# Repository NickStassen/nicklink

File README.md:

# NickLink v1.3

NickLink is a compact STM32F103C8T6 development and breakout board. Version 1.3 is a **34.0 × 25.5 mm, two-layer PCB** with an on-board **6-axis IMU (ST LSM6DSV)** for motion tracking, robotics and tap-to-wake projects. It also has two **2×10, 2.54 mm headers**, **four M2 mounting holes**, USB-C, RESET and BOOT buttons, a user LED, and **every header pin labelled on the front silkscreen**.

<details><summary>True size on a 27-inch 1440p monitor (view at 100% zoom)</summary>

</details>

**Real boards: v1.0 (left) vs v1.3 (right)**

**New board?** Follow the [bring-up guide](docs/BRINGUP.md): wiring for an STLINK-V3MINIE, a prebuilt USB DFU bootloader and test firmware, and a checklist for every part. After one ST-Link flash, the board is updated and tested over USB-C alone.

## What changed

**v1.3** adds the IMU on I2C1. It fits into existing gaps beside the MCU, on the top side with single-sided assembly. The board is 0.8 mm wider than v1.2 only because the pin labels grew to JLC's 1.0 mm minimum text height (see [JLCPCB design rules](#jlcpcb-design-rules)). PB6/PB7 get 4.7 kΩ pull-ups again, because the bus now has an on-board device. The IMU's INT1 drives PA0. The 3V3 budget drops by about 1 mA for the IMU. Everything else is as in v1.2.

**v1.3 reliability pass** (from a five-reviewer audit, the SPICE benches in [`sim/`](sim/) and ST's AN2586/AN4879 checklists):

- **Hot-plug damping:** R12, 1 Ω in series with VBUS, holds the USB hot-plug peak to 5.38 V and inrush under 50 µC. A ring on the 5V pin can still go higher. The regulator survives that because it is the 18 V TLV76733, not because every peak stays under 6 V.
- **Protected 5V pin:** J1.1 now has a 0.5 A polyfuse (F1) and a reverse-polarity P-MOSFET (Q1), so a short or a reversed supply no longer reaches VSYS unprotected.
- **D+ pull-up from VBUS** (AN4879 §3.1.1): it is present only while USB is plugged in. Powering from J1.1 no longer back-feeds the host.
- **Decoupling:** C4 at VDD3 is now 4.7 µF, as DS5319 requires. C12 (LDO input) is 4.7 µF, to keep inrush down.
- **User LED:** R6 is 330 Ω: about 1.3 mA instead of 0.4 mA, still within PC13's 3 mA sink limit.
- **Routing:** locked tracks for the USB-C orientation ties and the IMU's 3V3 feed. Every GND pad and pour island is checked for connection.

**Revision comparison:**

| | v1.1 | v1.2 | v1.3 |
|---|---|---|---|
| Outline | 34 × 33 mm (1122 mm²) | **33.19 × 25.5 mm** (846 mm², −25%) | **33.99 × 25.5 mm** (867 mm², −23%) |
| Pin labels | Numbered table on the back | **Name beside every pin on the front**; cheat sheet on the back | Same; 1.0 mm text (JLC minimum) |
| 5 V on the headers | None | **J1.1 = 5 V** (USB VBUS through a Schottky; also a 5 V input) | Same, plus a **0.5 A polyfuse and reverse-polarity protection** |
| USB power path | VBUS straight to the regulator | Schottky | **1 Ω hot-plug damping** + Schottky |
| Regulator | AMS1117-3.3 (SOT-223) + 22 µF tantalum | **TLV75533** (2×2 mm WSON) + ceramics | **TLV76733**, same package, input rated to 18 V |
| Reset | Header pin only | **RESET button** + NRST on J3 next to SWD | Same |
| Boot | BOOT0 slide switch | **BOOT button** (hold BOOT, tap RESET) | Same |
| SWD | Split across J1 and J3 | **All on J3**: 3V3, GND, SWDIO, SWCLK, SWO, NRST | Same |
| HSE crystal | 16 MHz | **8 MHz** (matches Blue Pill / STM32duino / CubeMX defaults) | Same |
| USB D+ pull-up | 1.5 kΩ to 3V3 | 1.5 kΩ to 3V3 | **From VBUS** (2.2k/4.7k), so no back-feed when powered from J1.1 |
| USB ESD | None | **USBLC6-2P6** on D+/D− and VBUS | Same |
| I2C pull-ups | 1.5 kΩ fitted on PB6/PB7 | Removed | **4.7 kΩ** (needed by the on-board IMU) |
| LEDs | Power | Power + **user LED on PC13** (low = on) | Same, brighter (330 Ω, about 1.3 mA) |
| IMU | — | — | **LSM6DSV** 6-axis accel + gyro with on-chip sensor fusion |
| Verification | — | DRC/ERC | DRC/ERC, SPICE benches ([`sim/`](sim/)), emulated test firmware ([`firmware/`](firmware/)) |

## Hardware

- STM32F103C8T6 (LQFP-48) with an 8 MHz crystal (12 pF load, 15 pF C0G caps): PLL ×9 = 72 MHz, USB clock 72 / 1.5 = 48 MHz.
- USB-C (GCT USB4085, through-hole) for power and USB full speed; 5.1 kΩ CC pull-downs for either orientation; D+ pull-up from VBUS (2.2 kΩ / 4.7 kΩ divider, 1.5 kΩ to 3.4 V, so it is present only while USB is plugged in); USBLC6-2P6 ESD array.
- Power path: USB VBUS → R12 1 Ω (hot-plug damping) → 1N5819WS Schottky → **VSYS** → TLV76733 LDO → **3V3** (J3.1, J1.20). VSYS also reaches the **5V pin** (J1.1) through a 0.5 A polyfuse (F1) and a reverse-polarity P-MOSFET (Q1). The Schottky stops a supply on the 5V pin from back-feeding the USB host.
- RESET button (NRST to GND, 100 nF), BOOT button (BOOT0 to 3V3, 10 kΩ pull-down), 10 kΩ pull-down on PB2/BOOT1.
- Red power LED, green user LED on PC13 (active low).
- **IMU:** ST LSM6DSV 6-axis accelerometer and gyroscope on I2C1 (PB6 SCL / PB7 SDA, address **0x6A**), INT1 to PA0.
- 33 GPIO + NRST on the headers. Only PA11/PA12 (USB) and PD0/PD1 (crystal) are not broken out.
- GND pours on both layers, stitched with vias.

## Header pinout

**Top view, USB at the top: J3 is left, J1 is right.** Pin 1 is the square pad at the upper left of each header; odd pins are the left column. The front silkscreen prints each pin's name right beside it (`A9` = PA9, `B12` = PB12, `RST` = NRST).

| Pin | J3 (left) | J1 (right) |
|---:|---|---|
| 1 | `3V3` 3V3 regulated output | `5V` 5 V (USB VBUS through Schottky + 0.5 A polyfuse; 4.5–5.5 V input, reverse-polarity protected) |
| 2 | `GND` | `GND` |
| 3 | `A9` PA9 / UART1 TX | `B15` PB15 / SPI2 MOSI |
| 4 | `A10` PA10 / UART1 RX | `B14` PB14 / SPI2 MISO |
| 5 | `A8` PA8 | `B13` PB13 / SPI2 SCK |
| 6 | `A15` PA15 | `B12` PB12 |
| 7 | `A13` PA13 / SWDIO | `B11` PB11 / I2C2 SDA / UART3 RX |
| 8 | `A14` PA14 / SWCLK | `B10` PB10 / I2C2 SCL / UART3 TX |
| 9 | `B3` PB3 / SWO | `B2` PB2 / BOOT1, 10k pull-down |
| 10 | `RST` NRST (reset, active low; 3.3 V only) | `B1` PB1 (3.3 V only) |
| 11 | `B4` PB4 | `B0` PB0 (3.3 V only) |
| 12 | `B5` PB5 (3.3 V only) | `A7` PA7 / SPI1 MOSI (3.3 V only) |
| 13 | `B6` PB6 / I2C1 SCL (4.7k pull-up, IMU; 3.3 V only) | `A6` PA6 / SPI1 MISO (3.3 V only) |
| 14 | `B7` PB7 / I2C1 SDA (4.7k pull-up, IMU; 3.3 V only) | `A5` PA5 / SPI1 SCK (3.3 V only) |
| 15 | `B8` PB8 / CAN RX (remap) | `A4` PA4 (3.3 V only) |
| 16 | `B9` PB9 / CAN TX (remap) | `A3` PA3 / UART2 RX (3.3 V only) |
| 17 | `C13` PC13 / user LED (3.3 V only) | `A2` PA2 / UART2 TX (3.3 V only) |
| 18 | `C14` PC14 (3.3 V only) | `A1` PA1 (3.3 V only) |
| 19 | `C15` PC15 (3.3 V only) | `A0` PA0 / WKUP / IMU INT1 via 10k (3.3 V only) |
| 20 | `GND` | `3V3` 3V3 regulated output |

Pins not marked "3.3 V only" are 5 V tolerant (FT) while the board is powered. B6/B7 are FT on the MCU but not at board level, because the IMU on that bus is limited to 3.6 V. PA1–PA7, PB0 and PB1 are also ADC inputs. PA0 is too, but it has the IMU interrupt on it (below). [`docs/pinout.csv`](docs/pinout.csv) has the same table in machine-readable form.

- **SWD:** J3.1 3V3 (target voltage sense), J3.2 GND, J3.7 SWDIO, J3.8 SWCLK, J3.10 NRST, optional J3.9 SWO.
- **USB bootloader:** the F103 has no factory USB DFU bootloader, so [`firmware/bootloader/`](firmware/bootloader/) adds one (dapboot, in the first 8 KiB of flash). Programs are linked at 0x08002000 and loaded over USB-C with `dfu-util`. Enter it with a double-tap of RESET, or J1.9 to 3V3 at reset.
- **Serial bootloader:** hold BOOT, tap RESET, release BOOT, then use USART1 on J3.3 (TX) / J3.4 (RX). This is ST's factory USART bootloader, in ROM, so it always works for recovery.
- **I2C1 / IMU:** I2C1 has on-board 4.7 kΩ pull-ups. External I2C modules can share the bus as long as they avoid address 0x6A and **pull up to 3.3 V only**. A 5 V module needs a level shifter, because the IMU's SCL/SDA limit is 3.6 V. If modules bring their own pull-ups, keep the combined value above about 1.5 kΩ. The 4.7 kΩ pull-ups meet the 400 kHz rise-time limit up to about 75 pF of bus capacitance (roughly 30 cm of wiring plus a few modules); for longer runs, use 100 kHz.
- **A0 has the IMU's INT1 on it through 10 kΩ.** INT1 drives low whenever no interrupt is asserted, so A0 always sees a 10 kΩ pull-down (also with INT1 set to open-drain, which only releases the pin while active-high). The interrupt is active high, matching WKUP's rising edge. You can still drive A0 from outside, or use it as an ADC input from a low-impedance source. Making A0 truly high-impedance needs INT1 set active-low open-drain (`H_LACTIVE` + `PP_OD`, IF_CFG 03h), which inverts the interrupt and stops it from waking the MCU through WKUP.
- **J3.6/J3.9/J3.11 (PA15/PB3/PB4) are JTAG pins at reset:** PA15 and PB4 have internal pull-ups and PB3 (JTDO/SWO) has none, until firmware frees them (`__HAL_AFIO_REMAP_SWJ_NOJTAG()` keeps SWD and releases them). PA13/PA14 stay SWD unless you disable SWJ completely, after which the debugger has to connect under reset (NRST is on J3.10).
- **User LED:** PC13 low turns it on. PC13–PC15 are low-drive pins (≤2 MHz) and must not source current. Their 3 mA sink limit is shared by all three pins (DS5319 Table 5), and the LED already takes about 1.3–1.8 mA of it. J3.17 carries the LED load, so an undriven PC13 floats around 1–1.5 V.

## IMU

The LSM6DSV is a 6-axis IMU: accelerometer up to ±16 g, gyroscope up to ±4000 dps.
- **Address:** I2C1 at 0x6A (SA0 tied low); CS is tied high for I2C mode.
- **Interrupt:** INT1 goes to PA0. PA0 is also the STM32's WKUP pin, so a tap or motion interrupt (rising edge) can wake the MCU from Standby.

### Axes

The IMU is placed at 0°, so its axes line up with the board and its readings need no remapping. Seen from the top with USB-C at the top edge (the same view as the [header pinout](#header-pinout)):

```
             USB-C
      +------[___]------+
      | J3           J1 |        +Y  toward USB-C
      | o o         o o |         ^
      | o o  [MCU]  o o |         |
      | o o     [U4]o o |         +----> +X  toward J1
      | o o         o o |        +Z  out of the component side, toward you
      +-----------------+
```

- **+X** points right, toward J1.
- **+Y** points up, toward the USB-C connector.
- **+Z** points out of the component side.

The axes are right-handed, and the gyroscope follows the right-hand rule. For example, positive gz is a counter-clockwise turn as seen from above. The accelerometer measures the reaction to gravity, so whichever axis points up reads +1 g:

| Board position | Reads +1 g on |
|---|---|
| Flat, components up | +Z |
| Flat, upside down | −Z |
| USB-C pointing up | +Y |
| USB-C pointing down | −Y |
| On its J3 edge (J1 up) | +X |
| On its J1 edge (J3 up) | −X |

The "flat" and "USB-C up" rows were measured on a v1.3 board; the rest follow from the right-handed axes. The test firmware's `imu` and `stream` commands report accel and gyro in these axes. [`firmware/imu_viewer.py`](firmware/README.md#3d-imu-viewer) shows the board's orientation live in 3D over USB-C.

Features useful here:
- **On-chip sensor fusion (SFLP):** outputs a game rotation vector (quaternion) at 15–480 Hz through the FIFO. The F103 has no hardware floating point, so this saves it doing the orientation math.
- **Hardware event detection:** tap, double-tap, wake-up, free-fall and 6D-orientation events, routable to INT1 (MD1_CFG 5Eh, with INTERRUPTS_ENABLE set in FUNCTIONS_ENABLE 50h). This covers tap-activated projects without polling.

Firmware starting points: ST's LSM6DSV platform-independent C driver, or the LSM6DSV16X one (`lsm6dsv16x-pid`) restricted to features the LSM6DSV has. Bring-up check: WHO_AM_I (0Fh) should read **0x70**.

**Why the LSM6DSV and not the LSM6DSV16X:** v1.3 was designed around the LSM6DSV16X (C5267406), but JLC lists that part as "Standard PCBA only" (X-ray inspection), and NickLink is an Economic PCBA board. The LSM6DSV (C41785564, which JLC lists as "LSM6DSVETR" and allows on Economic PCBA) is its sibling in the same LGA-14 package, with the same pinout, I2C-mode wiring, register map, WHO_AM_I and SFLP fusion. It lacks the LSM6DSV16X's machine-learning core, Qvar electrostatic sensing and analog hub. None of these is used here: Qvar and the analog hub need pins 2/3, which are tied to GND. The board and the test firmware are unchanged. ST's own store lists the part as LSM6DSV/LSM6DSVTR, so the "LSM6DSVETR" code is JLC's/LCSC's; confirm WHO_AM_I and SFLP output on the first boards.

Placement follows ST's LGA guidance: the IMU sits on the top side, with no ground pour or vias under the package, and only short pad-to-pad links at its edges. The local wiring is pre-routed; see docs/REVIEW.md. It sits in the right channel beside the MCU, below the RESET button, away from the regulator's heat and USB cable strain. ST's guidance of about 10 mm from screws (in its MEMS layout notes) can't be met on a board this small; H4 is about 2.4 mm from the IMU body. Mount on standoffs without over-tightening, since board flex shows up as accelerometer offset.

## Power

- **5V pin (J1.1), as an output:** VSYS through F1 (0.5 A hold, 1 A trip) and Q1. On USB that is VBUS minus the drop across R12, D2, F1 and Q1:
  - About 4.7 V at light load.
  - 4.2–4.4 V with 200 mA drawn from J1.1, from a 5.0 V port. From a 4.75 V port it is 4.0–4.1 V, so 5 V modules that need at least 4.5 V may not run.
  - A short from J1.1 to the adjacent GND pin trips F1 in about 0.1 s. VSYS collapses meanwhile, so the MCU resets once; the board recovers when the short is removed.
  - F1's hold current falls to about 0.33 A at 60 °C.
- **5V pin (J1.1), as an input:** apply 4.5–5.5 V and **do not exceed 5.5 V** in steady state. The parts behind it are rated higher (regulator 18 V, C12 and F1 16 V, Q1 gate ±12 V), so plug-in overshoot is survivable with normal leads. Q1 blocks a reversed supply, and F1 limits the current. D2 keeps J1.1 from back-feeding the USB host. With USB unplugged, the D+ pull-up is unpowered, so the host sees no device until USB is connected. Don't connect a battery to J1.1 while USB is plugged in: USB would charge it through F1 and Q1.
- **3V3 pins (J3.1, J1.20):** LDO outputs. Budget about **250 mA total including the MCU** when powered from USB. That figure is an estimate for this two-layer board (with two thermal vias under the LDO), not a measured limit. From a 5.5 V input on J1.1, keep below about 200 mA. **Do not feed 3V3 in from outside**: the regulator isn't specified for reverse current.
- **Hot-plug:** cables ring when plugged into a live supply. SPICE (`sim/` benches 11 and 12):
  - **USB:** with R12 fitted, the worst-case regulator input peak is 5.38 V for cables up to 1 µH (6.1–11.4 V without R12), and 7.3 V for an unusually long 3 µH cable. Inrush is 33 µC (USB limit 50 µC). R12 costs about 0.25 V of headroom at 250 mA.
  - **J1.1:** this path has no R12, so plugging a live supply onto J1.1 rings VSYS to about 5.4–9 V. That is why the regulator is the 18 V TLV76733.
  - **Bench leads over about 1 µH:** with these on J1.1, connect first and then switch the supply on. The most pessimistic capacitor model puts the ring past Q1's 12 V gate rating.

## Mounting

Four 2.2 mm holes for M2 screws. The keep-out is sized for **button-head (ISO 7380, 3.5 mm head)** screws and standoffs up to 4 mm across. Coordinates are measured from the board's upper-left corner, top view, X right, Y down.

| Hole | X (mm) | Y (mm) |
|---|---:|---:|
| H1 | 9.93 | 2.05 |
| H2 | 24.06 | 2.05 |
| H3 | 9.93 | 23.45 |
| H4 | 24.06 | 23.45 |

The USB-C receptacle overhangs the top edge by about 2 mm, as in v1.1.

## Open and edit

Open [`nicklink.kicad_pro`](nicklink.kicad_pro) in **KiCad 10**. The schematic, PCB, rules and project-local footprints (`nicklink.pretty/`) are included.

NickLink is generated by scripts in [`tools/`](tools/README.md). [`tools/spec.py`](tools/spec.py) is the single source of truth for parts, nets and header pinout, and [`tools/placement.py`](tools/placement.py) holds component positions. `tools/build_all.sh` regenerates the schematic, places parts, autoroutes with Freerouting, stitches the GND pours and runs DRC. It writes `nicklink.kicad_pcb` only if everything is clean. Everything runs in Docker (`kicad/kicad:10.0`); no local KiCad install is needed.

| Location | Contents |
|---|---|
| `nicklink.kicad_sch` / `.kicad_pcb` / `.kicad_pro` | Generated schematic, routed board, design rules |
| `nicklink.pretty/` | Project footprints: USB4085, plus header and button copies without silkscreen (the board draws its own labels) |
| `tools/` | Build pipeline, see [tools/README.md](tools/README.md) |
| `docs/` | [Design review](docs/REVIEW.md), pinout CSV, schematic, assembly and copper PDFs, renders |
| `fabrication/v1.3/` | Gerbers, drills, JLC BOM and CPL |
| `fabrication/v1.1/`, `v1.2/` | Previous revisions' outputs, kept for reference |
| `checks/` | Saved DRC/ERC reports for v1.3 |

## JLCPCB design rules

The board is checked against JLCPCB's published 2-layer and assembly limits ([PCB capabilities](https://jlcpcb.com/capabilities/pcb-capabilities), [assembly capabilities](https://jlcpcb.com/capabilities/pcb-assembly-capabilities), checked 2026-10-01). The limits are encoded in the board setup and `nicklink.kicad_dru`, so every DRC run enforces them.

| JLC limit | NickLink |
|---|---|
| Trace / space ≥ 0.10 / 0.10 mm | ≥ 0.10 mm tracks (0.127 mm signals, 0.2 mm GND and 3V3, 0.3 mm VBUS/5 V), 0.127 mm clearance |
| Via ≥ 0.15 mm drill / 0.25 mm diameter | 0.3 / 0.6 mm |
| Component PTH annular ring ≥ 0.18 mm | ≥ 0.18 mm. The USB4085 pads change from GCT's 0.40/0.65 mm (0.125 mm ring) to a 0.38 mm hole in a 0.74 mm pad, which stays within GCT's 0.40 ± 0.05 mm hole spec for the 0.22 × 0.15 mm pins. The pad gap is 0.11 mm, above JLC's 0.10 mm. The LDO's two thermal vias are 0.3 mm in 0.66 mm pads. |
| Pad hole-to-hole ≥ 0.45 mm; plated slot ≥ 0.5 mm | ≥ 0.47 mm (USB4085 0.85 mm pitch, 0.38 mm holes); 0.6 mm shield slots |
| SMD pad to pad ≥ 0.15 mm | ≥ 0.15 mm (the IMU's LGA is the tightest) |
| Copper to routed edge ≥ 0.2 mm (≥ 0.3 mm for Economic assembly) | 0.3 mm |
| Solder-mask web ≥ 0.10 mm | 0.10 mm minimum checked |
| Silkscreen line ≥ 0.15 mm, text ≥ 1.0 mm, silk to pad ≥ 0.15 mm | All silk ≥ 0.15 mm wide; labels 1.0 mm tall; labels 0.15 mm from pads and the edge. The library 0402 footprints' own silk sits about 0.09 mm from their pads; JLC clips it. |
| Component bodies ≥ 0.3 mm apart, IPC-7351B medium density | KiCad library courtyards (IPC nominal), none overlapping |
| Economic assembly: components ≥ 0.3 mm from edge, pitch ≥ 0.4 mm, passives ≥ 0201 | SMD bodies ≥ 1 mm from the edge; finest pitch 0.5 mm; 0402 passives |

**Ordering:**
- Under 70 × 70 mm, so order **Economic PCBA**. Economic needs no on-board fiducials or rails. JLC can add edge rails and fiducials if you choose Standard or panelize; on-board fiducials would need 3.85 mm from the edge.
- Choose an **ENIG** finish: the 0.5 mm-pitch LGA and LQFP solder more reliably on a flat pad than on HASL. On Economic PCBA, 1.6 mm ENIG comes only with **green** solder mask. Avoid black or white anyway: JLC only keeps a mask bridge between pads 0.13 mm or more apart on those colours (0.10 mm on green), and the USB-C pads are 0.11 mm apart.
- The CPL is in Gerber coordinates, so JLC aligns it to the board without an "offset" prompt. Its rotations and positions are corrected per LCSC part for JLC's own footprints (`JLC_ROT`/`JLC_OFS` in `tools/fab.sh`: LQFP-48 −90°; SOT-666 and SOT-323 +180°; the 2×10 headers −90° and centred; USB4085 origin offset). Still check the pin-1 marks in JLC's placement preview.
- JLC also assembles the through-hole parts (USB-C, headers; wave soldered), so the BOM has one line per LCSC part, THT included. The USB-C GND pins use thermal reliefs, which also helps if you ever hand-solder a replacement.
- Signal tracks, and VBUS_D (USB power) under H1, pass under the M2 screw heads (under solder mask, vias tented). Use plastic standoffs or washers if you clamp with metal hardware.

## Validation and fabrication

KiCad 10.0.6: **0 DRC violations, 0 unconnected items, 0 schematic-parity issues, 0 ERC errors or warnings** (reports in [`checks/`](checks/)). Every pin in the schematic netlist is checked against `tools/spec.py`. These checks cover connectivity and geometry. This revision has not been built yet; it needs a prototype and bench testing (see [`docs/BRINGUP.md`](docs/BRINGUP.md)).

The BOM carries verified LCSC part numbers for every part, through-hole included. To order, upload `fabrication/v1.3/nicklink_gerbers.zip`, then for assembly `nicklink_BOM_JLC.csv` and `nicklink_CPL.csv`. Several parts are JLC "Extended" parts, which add a per-part loading fee; see [`tools/parts_research.md`](tools/parts_research.md).

**Bring-up and board test:** [`docs/BRINGUP.md`](docs/BRINGUP.md) walks through the first power-up of a new board, wiring an STLINK-V3MINIE to J3 once to flash the USB bootloader and test firmware ([`firmware/prebuilt/`](firmware/prebuilt/)), and a checklist run over USB-C. The checklist covers power, crystal, LEDs, buttons, USB, IMU, every header GPIO, ADC and Standby wake.

**Interface limits:**

- USB and CAN cannot run at the same time on the F103 (they share packet RAM).
- **I2C1 is always in use by the IMU (PB6/PB7).**
  - Remapping SPI1 to PA15/PB3/PB4/PB5 while I2C1 is clocked breaks MOSI on PB5 (erratum ES096). Gate the I2C1 clock off while SPI1 is remapped.
  - Using PB6/PB7 for USART1-remap or TIM4 disturbs the IMU's bus.
  - Remapping I2C1 to PB8/PB9 disconnects the IMU and takes the CAN pins.
- **Never set the IMU's `IF_CFG.I2C_I3C_disable` bit.** With CS tied high and no power switch on the IMU, only a full power cycle recovers it.
- CAN uses PB8/PB9 through the remap and needs an external transceiver.
- USB impedance and compliance are not qualified.

**Firmware notes for reliability:**

- The F103 has power-on/power-down reset but **no brown-out reset**. Enable the PVD (for example at 2.9 V) and stop flash writes when it trips.
- Enable the clock security system (CSS). If the HSE fails, the MCU falls back to HSI. USB cannot run from HSI, so treat that as a fault.
- Do not drive header pins while the board is unpowered. Keep injected current within ±5 mA per pin; PA4, PA5 and PC13–PC15 tolerate none.
- Set unused pins to analog input (the lowest-power, defined state) and free JTAG with `NOJTAG` if PA15/PB3/PB4 are used as GPIO.

**Simulation and test firmware:** [`sim/`](sim/) holds ngspice benches for hot-plug, LDO, brown-out, reset, LEDs, I2C, VDDA and the crystal, with results in `sim/results/summary.md`. [`firmware/`](firmware/) is a bring-up firmware for this pinout. It exercises the user LED, RESET, every header GPIO, the IMU (including tap wake on A0), USART1 and the HSE/PLL with HSI fallback, and runs under Renode emulation (`firmware/test.sh`) before you flash the real board.

## References

- [ST STM32F103x8/xB datasheet](https://www.st.com/resource/en/datasheet/stm32f103c8.pdf)
- [ST AN2586 — hardware design](https://www.st.com/resource/en/application_note/an2586-getting-started-with-stm32f10xxx-hardware-development-stmicroelectronics.pdf)
- [ST AN2867 — oscillator design](https://www.st.com/resource/en/application_note/an2867-guidelines-for-oscillator-design-on-stm8afals-and-stm32-mcusmpus-stmicroelectronics.pdf)
- [TI TLV767 datasheet](https://www.ti.com/lit/ds/symlink/tlv767.pdf) (U2 from v1.3); [TLV755P](https://www.ti.com/lit/ds/symlink/tlv755p.pdf) (v1.2)
- [ST LSM6DSV datasheet](https://www.st.com/resource/en/datasheet/lsm6dsv.pdf)
- [ST USBLC6-2 datasheet](https://www.st.com/resource/en/datasheet/usblc6-2.pdf)

Licensed under the [MIT License](LICENSE).

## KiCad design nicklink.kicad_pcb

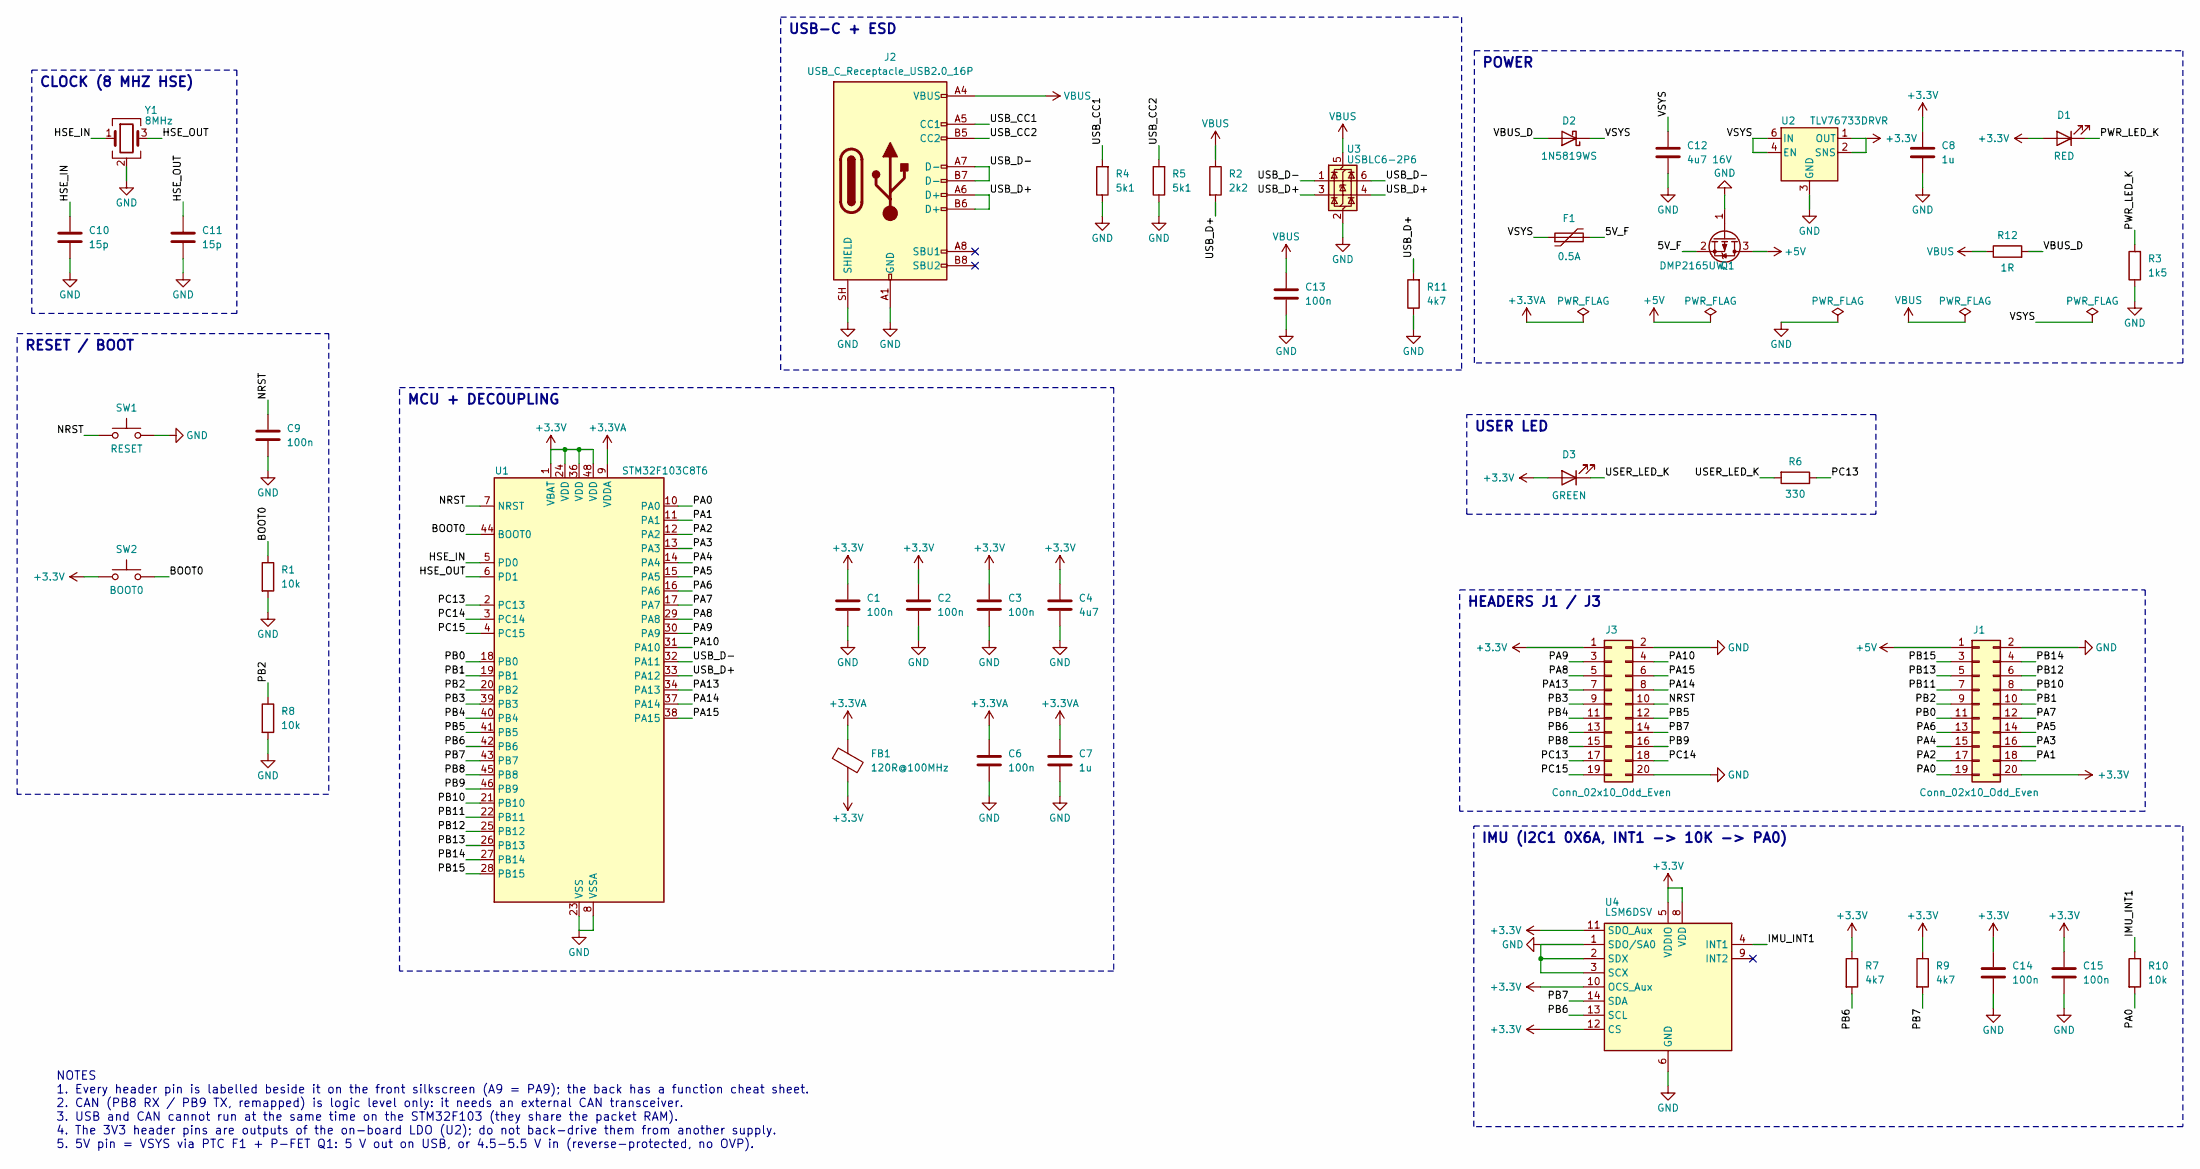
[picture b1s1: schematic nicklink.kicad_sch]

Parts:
C1, C2, C3, C6, C9, C13, C14, C15: 100n; C_0402_1005Metric; LCSC C1525
C4: 4u7; C_0402_1005Metric; LCSC C23733
C7, C8: 1u; C_0402_1005Metric; LCSC C52923
C10, C11: 15p; C_0402_1005Metric; LCSC C1548
C12: 4u7 16V; C_0402_1005Metric; MPN Samsung CL05A475MO5NUNC; LCSC C318563
D1: RED; LED_0402_1005Metric; MPN Everlight 16-213/R6C-AQ2R2B/3T; LCSC C264407
D2: 1N5819WS; D_SOD-323; LCSC C191023
D3: GREEN; LED_0402_1005Metric; MPN Everlight 16-213/GHC-YR1S1/3T; LCSC C74338
F1: 0.5A; Fuse_0805_2012Metric; MPN LUTE 0805L050/16XR; LCSC C22435898
FB1: 120R@100MHz; L_0402_1005Metric; LCSC C85812
J1, J3: Conn_02x10_Odd_Even; PinHeader_2x10_P2.54mm_Vertical_NoSilk; MPN HanElectricity 2541WV-2x10P (male, 6 mm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; LCSC C5383109
J2: USB_C_Receptacle_USB2.0_16P; USB_C_Receptacle_GCT_USB4085_EdgeSilk; MPN GCT USB4085-GF-A; LCSC C7095263
Q1: DMP2165UW; SOT-323_SC-70_NoSilk; MPN Diodes DMP2165UW-7; LCSC C388477
R1, R10: 10k; R_0402_1005Metric; LCSC C25744
R2: 2k2; R_0402_1005Metric; LCSC C25879
R3: 1k5; R_0402_1005Metric; LCSC C25867
R4: 5k1; R_0402_1005Metric; LCSC C25905
R5: 5k1; R_0402_1005Metric_NoSilk; LCSC C25905
R6: 330; R_0402_1005Metric; LCSC C25104
R7, R9: 4k7; R_0402_1005Metric; LCSC C25900
R8: 10k; R_0402_1005Metric_NoSilk; LCSC C25744
R11: 4k7; R_0402_1005Metric_NoSilk; LCSC C25900
R12: 1R; R_0805_2012Metric; MPN YAGEO SR0805FR-471RL; LCSC C873764
SW1: RESET; SW_SPST_B3U-1000P_NoSilk; LCSC C231329
SW2: BOOT0; SW_SPST_B3U-1000P_NoSilk; LCSC C231329
U1: STM32F103C8T6; LQFP-48_7x7mm_P0.5mm; LCSC C8734
U2: TLV76733DRVR; WSON-6-1EP_2x2mm_P0.65mm_EP1x1.6mm_ThermalVias03; MPN TI TLV76733DRVR; LCSC C2848334
U3: USBLC6-2P6; SOT-666; LCSC C15999
U4: LSM6DSV; LGA-14_3x2.5mm_P0.5mm_LayoutBorder3x4y_NoSilk; MPN ST LSM6DSV (JLC: LSM6DSVETR); LCSC C41785564
Y1: 8MHz; Crystal_SMD_3225-4Pin_3.2x2.5mm; MPN YXC X32258MOB4SI (CL 12 pF); LCSC C2682775

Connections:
+3.3V: C1.1, C2.1, C3.1, C4.1, C8.1, C14.1, C15.1, D1.2 (A), D3.2 (A), FB1.2, J1.20, J3.1, R7.1, R9.1, SW2.1, U1.1 (VBAT), U1.24 (VDD), U1.36 (VDD), U1.48 (VDD), U2.1 (OUT), U2.2 (SNS), U4.5 (VDDIO), U4.8 (VDD), U4.10 (OCS_Aux), U4.11 (SDO_Aux), U4.12 (CS)
+3.3VA: C6.1, C7.1, FB1.1, U1.9 (VDDA)
+5V: J1.1, Q1.3 (D)
/5V_F: F1.2, Q1.2 (S)
/BOOT0: R1.1, SW2.2, U1.44 (BOOT0)
/HSE_IN: C10.1, U1.5 (PD0), Y1.1
/HSE_OUT: C11.1, U1.6 (PD1), Y1.3
/IMU_INT1: R10.1, U4.4 (INT1)
/NRST: C9.1, J3.10, SW1.1, U1.7 (NRST)
/PA0: J1.19, R10.2, U1.10 (PA0)
/PA1: J1.18, U1.11 (PA1)
/PA2: J1.17, U1.12 (PA2)
/PA3: J1.16, U1.13 (PA3)
/PA4: J1.15, U1.14 (PA4)
/PA5: J1.14, U1.15 (PA5)
/PA6: J1.13, U1.16 (PA6)
/PA7: J1.12, U1.17 (PA7)
/PA8: J3.5, U1.29 (PA8)
/PA9: J3.3, U1.30 (PA9)
/PA10: J3.4, U1.31 (PA10)
/PA13: J3.7, U1.34 (PA13)
/PA14: J3.8, U1.37 (PA14)
/PA15: J3.6, U1.38 (PA15)
/PB0: J1.11, U1.18 (PB0)
/PB1: J1.10, U1.19 (PB1)
/PB2: J1.9, R8.1, U1.20 (PB2)
/PB3: J3.9, U1.39 (PB3)
/PB4: J3.11, U1.40 (PB4)
/PB5: J3.12, U1.41 (PB5)
/PB6: J3.13, R7.2, U1.42 (PB6), U4.13 (SCL)
/PB7: J3.14, R9.2, U1.43 (PB7), U4.14 (SDA)
/PB8: J3.15, U1.45 (PB8)
/PB9: J3.16, U1.46 (PB9)
/PB10: J1.8, U1.21 (PB10)
/PB11: J1.7, U1.22 (PB11)
/PB12: J1.6, U1.25 (PB12)
/PB13: J1.5, U1.26 (PB13)
/PB14: J1.4, U1.27 (PB14)
/PB15: J1.3, U1.28 (PB15)
/PC13: J3.17, R6.1, U1.2 (PC13)
/PC14: J3.18, U1.3 (PC14)
/PC15: J3.19, U1.4 (PC15)
/PWR_LED_K: D1.1 (K), R3.2
/USB_CC1: J2.A5 (CC1), R4.2
/USB_CC2: J2.B5 (CC2), R5.2
/USB_D+: J2.A6 (D+), J2.B6 (D+), R2.2, R11.2, U1.33 (PA12), U3.3 (I/O2), U3.4 (I/O2)
/USB_D-: J2.A7 (D-), J2.B7 (D-), U1.32 (PA11), U3.1 (I/O1), U3.6 (I/O1)
/USER_LED_K: D3.1 (K), R6.2
/VBUS_D: D2.2 (A), R12.2
/VSYS: C12.1, D2.1 (K), F1.1, U2.4 (EN), U2.6 (IN)
GND: C1.2, C2.2, C3.2, C4.2, C6.2, C7.2, C8.2, C9.2, C10.2, C11.2, C12.2, C13.2, C14.2, C15.2, J1.2, J2.A1 (GND), J2.A12 (GND), J2.B1 (GND), J2.B12 (GND), J2.SH (SHIELD), J3.2, J3.20, Q1.1 (G), R1.2, R3.1, R4.1, R5.1, R8.2, R11.1, SW1.2, U1.8 (VSSA), U1.23 (VSS), U1.35 (VSS), U1.47 (VSS), U2.3 (GND), U2.5 (GND), U2.7 (GND), U3.2 (GND), U4.1 (SDO/SA0), U4.2 (SDX), U4.3 (SCX), U4.6 (GND), U4.7 (GND), Y1.2 (G), Y1.4 (G)
VBUS: C13.1, J2.A4 (VBUS), J2.A9 (VBUS), J2.B4 (VBUS), J2.B9 (VBUS), R2.1, R12.1, U3.5 (VBUS)

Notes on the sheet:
CLOCK (8 MHZ HSE)
RESET / BOOT
MCU + DECOUPLING
USB-C + ESD
POWER
USER LED
HEADERS J1 / J3
IMU (I2C1 0X6A, INT1 -> 10K -> PA0)
NOTES 1. Every header pin is labelled beside it on the front silkscreen (A9 = PA9); the back has a function cheat sheet. 2. CAN (PB8 RX / PB9 TX, remapped) is logic level only: it needs an external CAN transceiver. 3. USB and CAN cannot run at the same time on the STM32F103 (they share the packet R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

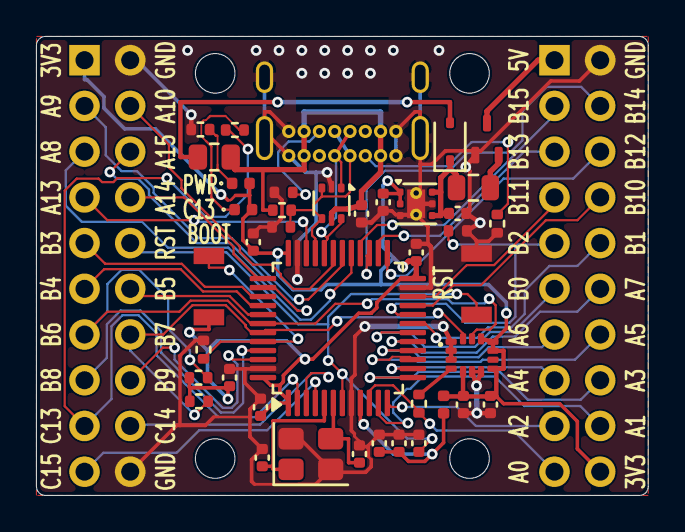
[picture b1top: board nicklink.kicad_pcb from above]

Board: 2 copper layers, 34.0 x 25.5 mm, 46 parts (0 on the bottom side), 52 nets.

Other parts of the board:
H1: H1; MountingHole_2.2mm_M2_ISO7380
H2: H2; MountingHole_2.2mm_M2_ISO7380
H3: H3; MountingHole_2.2mm_M2_ISO7380
H4: H4; MountingHole_2.2mm_M2_ISO7380

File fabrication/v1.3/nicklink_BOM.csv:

Comment,Designator,Footprint,LCSC Part #,Notes,Assembly
100n,"C1,C2,C3,C6,C9,C13,C14,C15",C_0402_1005Metric,C1525,"C1: VDD pin 1/VBAT decoupling; C2: VDD pin 24 decoupling; C3: VDD pin 36 decoupling; C6: VDDA; C13: USBLC6 VBUS decoupling; C14,C15: IMU VDD/VDDIO",SMD
4u7,C4,C_0402_1005Metric,C23733,VDD3 (pin 48) bulk: DS5319 Fig. 14 requires 4.7 uF on VDD3,SMD
1u,"C7,C8",C_0402_1005Metric,C52923,C7: VDDA; C8: LDO output,SMD
15p,"C10,C11",C_0402_1005Metric,C1548,C0G; crystal CL 12 pF,SMD
4u7 16V,C12,C_0402_1005Metric,C318563,"Samsung CL05A475MO5NUNC; LDO input, 16 V X5R (J1.1 hot-plug ring); USB allows <= 10 uF",SMD
RED,D1,LED_0402_1005Metric,C264407,Everlight 16-213/R6C-AQ2R2B/3T; Power,SMD
1N5819WS,D2,D_SOD-323,C191023,Blocks back-feed from VSYS / the 5V pin into USB,SMD
GREEN,D3,LED_0402_1005Metric,C74338,"Everlight 16-213/GHC-YR1S1/3T; User LED, PC13 low = on",SMD
0.5A,F1,Fuse_0805_2012Metric,C22435898,"LUTE 0805L050/16XR; 5V pin short / reverse-supply limit: Ihold 0.5 A, Itrip 1 A, 16 V",SMD
120R@100MHz,FB1,L_0402_1005Metric,C85812,,SMD
Conn_02x10_Odd_Even,"J1,J3",PinHeader_2x10_P2.54mm_Vertical_NoSilk,C5383109,"HanElectricity 2541WV-2x10P (male, 6 mm pins, 3 mm tail)",THT
USB_C_Receptacle_USB2.0_16P,J2,USB_C_Receptacle_GCT_USB4085_EdgeSilk,C7095263,GCT USB4085-GF-A,THT
DMP2165UW,Q1,SOT-323_SC-70_NoSilk,C388477,Diodes DMP2165UW-7; 5V pin reverse-polarity switch (gate to GND),SMD
10k,"R1,R8,R10",R_0402_1005Metric,C25744,R1: BOOT0 pull-down; R10: IMU INT1 isolation; R8: BOOT1 pull-down,SMD
2k2,R2,R_0402_1005Metric,C25879,"USB FS D+ pull-up (with R11: 1.5k to 3.4 V, VBUS-derived)",SMD
1k5,R3,R_0402_1005Metric,C25867,,SMD
5k1,"R4,R5",R_0402_1005Metric,C25905,,SMD
330,R6,R_0402_1005Metric,C25104,~1.2-1.8 mA (PC13 sinks <= 3 mA),SMD
4k7,"R7,R9,R11",R_0402_1005Metric,C25900,R7: I2C1 SCL pull-up; R9: I2C1 SDA pull-up; R11: D+ pull-up divider; VBUS bleed,SMD
1R,R12,R_0805_2012Metric,C873764,"YAGEO SR0805FR-471RL; Hot-plug damping (anti-surge, 500 mW)",SMD
BOOT0/RESET,"SW1,SW2",SW_SPST_B3U-1000P_NoSilk,C231329,SW2: Hold while resetting to enter the USART1 system bootloader,SMD
STM32F103C8T6,U1,LQFP-48_7x7mm_P0.5mm,C8734,,SMD
TLV76733DRVR,U2,WSON-6-1EP_2x2mm_P0.65mm_EP1x1.6mm_ThermalVias03,C2848334,TI TLV76733DRVR,SMD
USBLC6-2P6,U3,SOT-666,C15999,,SMD
LSM6DSV,U4,LGA-14_3x2.5mm_P0.5mm_LayoutBorder3x4y_NoSilk,C41785564,ST LSM6DSV (JLC: LSM6DSVETR),SMD
8MHz,Y1,Crystal_SMD_3225-4Pin_3.2x2.5mm,C2682775,YXC X32258MOB4SI (CL 12 pF),SMD

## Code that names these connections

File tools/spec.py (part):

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    # --- MCU ---------------------------------------------------------------
    "U1": ("MCU_ST_STM32F1:STM32F103C8Tx", "STM32F103C8T6", "Package_QFP:LQFP-48_7x7mm_P0.5mm", {
        "1": "+3.3V",  # VBAT, no backup battery
        "2": "PC13", "3": "PC14", "4": "PC15",
        "5": "HSE_IN", "6": "HSE_OUT", "7": "NRST",
        "8": "GND", "9": "+3.3VA",
        "10": "PA0", "11": "PA1", "12": "PA2", "13": "PA3", "14": "PA4",
        "15": "PA5", "16": "PA6", "17": "PA7", "18": "PB0", "19": "PB1",
        "20": "PB2", "21": "PB10", "22": "PB11", "23": "GND", "24": "+3.3V",
        "25": "PB12", "26": "PB13", "27": "PB14", "28": "PB15",
        "29": "PA8", "30": "PA9", "31": "PA10", "32": "USB_D-", "33": "USB_D+",
        "34": "PA13", "35": "GND", "36": "+3.3V",
        "37": "PA14", "38": "PA15", "39": "PB3", "40": "PB4", "41": "PB5",
        "42": "PB6", "43": "PB7", "44": "BOOT0", "45": "PB8", "46": "PB9",
        "47": "GND", "48": "+3.3V",
    }, {}),
    "C1": ("Device:C", "100n", "Capacitor_SMD:C_0402_1005Metric", {"1": "+3.3V", "2": "GND"}, {"Note": "VDD pin 1/VBAT decoupling"}),
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    "C7": ("Device:C", "1u", "Capacitor_SMD:C_0402_1005Metric", {"1": "+3.3VA", "2": "GND"}, {"Note": "VDDA"}),

    # --- Clock: 8 MHz HSE ---------------------------------------------------
    "Y1": ("Device:Crystal_GND24", "8MHz", "Crystal:Crystal_SMD_3225-4Pin_3.2x2.5mm", {"1": "HSE_IN", "2": "GND", "3": "HSE_OUT", "4": "GND"}, {"MPN": "YXC X32258MOB4SI (CL 12 pF)"}),
    "C10": ("Device:C", "15p", "Capacitor_SMD:C_0402_1005Metric", {"1": "HSE_IN", "2": "GND"}, {"Note": "C0G; crystal CL 12 pF"}),
    "C11": ("Device:C", "15p", "Capacitor_SMD:C_0402_1005Metric", {"1": "HSE_OUT", "2": "GND"}, {"Note": "C0G; crystal CL 12 pF"}),

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    "C9": ("Device:C", "100n", "Capacitor_SMD:C_0402_1005Metric", {"1": "NRST", "2": "GND"}, {}),
    "SW2": ("Switch:SW_Push", "BOOT0", "nicklink:SW_SPST_B3U-1000P_NoSilk", {"1": "+3.3V", "2": "BOOT0"}, {"Note": "Hold while resetting to enter the USART1 system bootloader"}),
    "R1": ("Device:R", "10k", "Resistor_SMD:R_0402_1005Metric", {"1": "BOOT0", "2": "GND"}, {"Note": "BOOT0 pull-down"}),
    "R8": ("Device:R", "10k", "nicklink:R_0402_1005Metric_NoSilk", {"1": "PB2", "2": "GND"}, {"Note": "BOOT1 pull-down"}),

    # --- USB ----------------------------------------------------------------
    "J2": ("Connector:USB_C_Receptacle_USB2.0_16P", "USB_C_Receptacle_USB2.0_16P", "nicklink:USB_C_Receptacle_GCT_USB4085_EdgeSilk", {
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    # R12 damps the USB cable inductance against the ceramic input caps on hot-plug (sim bench 11:
    # without it the input rings to about 6.1-11.4 V; with 1.0 ohm and C12 4.7 uF the USB peak is 5.38 V).
    # The fitted regulator is the TLV76733 (VIN/EN abs max 18 V). The 6.0 V figure was the TLV755 it replaced.
    "R12": ("Device:R", "1R", "Resistor_SMD:R_0805_2012Metric", {"1": "VBUS", "2": "VBUS_D"}, {"Note": "Hot-plug damping (anti-surge, 500 mW)", "MPN": "YAGEO SR0805FR-471RL"}),
    "D2": ("Device:D_Schottky", "1N5819WS", "Diode_SMD:D_SOD-323", {"1": "VSYS", "2": "VBUS_D"}, {"Note": "Blocks back-feed from VSYS / the 5V pin into USB"}),  # 1=K, 2=A
    "C12": ("Device:C", "4u7 16V", "Capacitor_SMD:C_0402_1005Metric", {"1": "VSYS", "2": "GND"}, {"Note": "LDO input, 16 V X5R (J1.1 hot-plug ring); USB allows <= 10 uF", "MPN": "Samsung CL05A475MO5NUNC"}),
    "F1": ("Device:Polyfuse", "0.5A", "Fuse:Fuse_0805_2012Metric", {"1": "VSYS", "2": "5V_F"}, {"Note": "5V pin short / reverse-supply limit: Ihold 0.5 A, Itrip 1 A, 16 V", "MPN": "LUTE 0805L050/16XR"}),
    # SOT-323 G-S-D = 1-2-3, same as the library's DMG2301L symbol (SOT-23); footprint overridden.
    "Q1": ("Transistor_FET:DMG2301L", "DMP2165UW", "nicklink:SOT-323_SC-70_NoSilk", {"1": "GND", "2": "5V_F", "3": "+5V"}, {"Note": "5V pin reverse-polarity switch (gate to GND)", "MPN": "Diodes DMP2165UW-7"}),
    # TLV76733DRVR (WSON-6 2x2, DRV0006A like the TLV755): 1 OUT, 2 SNS (tie to OUT), 3 GND, 4 EN, 5 GND,
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    # --- LEDs ---------------------------------------------------------------
    "D1": ("Device:LED", "RED", "LED_SMD:LED_0402_1005Metric", {"1": "PWR_LED_K", "2": "+3.3V"}, {"Note": "Power", "MPN": "Everlight 16-213/R6C-AQ2R2B/3T"}),  # 1=K, 2=A
    "R3": ("Device:R", "1k5", "Resistor_SMD:R_0402_1005Metric", {"1": "GND", "2": "PWR_LED_K"}, {}),
    "D3": ("Device:LED", "GREEN", "LED_SMD:LED_0402_1005Metric", {"1": "USER_LED_K", "2": "+3.3V"}, {"Note": "User LED, PC13 low = on", "MPN": "Everlight 16-213/GHC-YR1S1/3T"}),
    "R6": ("Device:R", "330", "Resistor_SMD:R_0402_1005Metric", {"1": "PC13", "2": "USER_LED_K"}, {"Note": "~1.2-1.8 mA (PC13 sinks <= 3 mA)"}),

    # --- IMU: LSM6DSV on I2C1 (address 0x6A), INT1 -> PA0 (WKUP) ----------------
    # Project symbol (nicklink.kicad_sym): KiCad has none; same LGA-14 pinout as LSM6DSM.
    # LSM6DSV (DS13476), not the LSM6DSV16X it replaced: JLC lists the LSM6DSV16X (C5267406) as
    # "Standard PCBA only". Same pinout, register map, WHO_AM_I 0x70 and SFLP sensor fusion; it lacks
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    "U4": ("nicklink:LSM6DSV", "LSM6DSV", "nicklink:LGA-14_3x2.5mm_P0.5mm_LayoutBorder3x4y_NoSilk", {
        "1": "GND",          # SDO/SA0 low -> I2C address 0x6A
        "2": "GND", "3": "GND",  # SDx/SCx aux bus unused
        "4": "IMU_INT1",     # INT1 -> R10 -> PA0 (INT1 drives low by default)
        "5": "+3.3V", "8": "+3.3V",  # VDDIO, VDD
        "6": "GND", "7": "GND",
        "10": "+3.3V", "11": "+3.3V",  # OCS_Aux/SDO_Aux: "connect to Vdd_IO or leave unconnected" (DS13476 Table 2)
        "12": "+3.3V",       # CS high -> I2C mode
        "13": "PB6", "14": "PB7",
    }, {"MPN": "ST LSM6DSV (JLC: LSM6DSVETR)"}),
    "C14": ("Device:C", "100n", "Capacitor_SMD:C_0402_1005Metric", {"1": "+3.3V", "2": "GND"}, {"Note": "IMU VDD/VDDIO"}),
    "C15": ("Device:C", "100n", "Capacitor_SMD:C_0402_1005Metric", {"1": "+3.3V", "2": "GND"}, {"Note": "IMU VDD/VDDIO"}),
    # INT1 is "output forced to ground" from power-up until firmware configures the IMU;
    # 10k keeps that from fighting whatever a user connects to A0 (it becomes a weak pull-down).
    "R10": ("Device:R", "10k", "Resistor_SMD:R_0402_1005Metric", {"1": "IMU_INT1", "2": "PA0"}, {"Note": "IMU INT1 isolation"}),
    "R7": ("Device:R", "4k7", "Resistor_SMD:R_0402_1005Metric", {"1": "+3.3V", "2": "PB6"}, {"Note": "I2C1 SCL pull-up"}),
    "R9": ("Device:R", "4k7", "Resistor_SMD:R_0402_1005Metric", {"1": "+3.3V", "2": "PB7"}, {"Note": "I2C1 SDA pull-up"}),

    # --- Headers ------------------------------------------------------------
    # Top view, USB up: J3 left, J1 right. Pin 1 upper-left; odd pins = left column. JLC assembles them (THT).
    "J1": ("Connector_Generic:Conn_02x10_Odd_Even", "Conn_02x10_Odd_Even", "nicklink:PinHeader_2x10_P2.54mm_Vertical_NoSilk", {
        "1": "+5V", "2": "GND",
        "3": "PB15", "4": "PB14", "5": "PB13", "6": "PB12",
        "7": "PB11", "8": "PB10", "9": "PB2", "10": "PB1",
        "11": "PB0", "12": "PA7", "13": "PA6", "14": "PA5",
        "15": "PA4", "16": "PA3", "17": "PA2", "18": "PA1",
        "19": "PA0", "20": "+3.3V",
    }, {"MPN": "HanElectricity 2541WV-2x10P (male, 6 mm pins, 3 mm tail)"}),
    "J3": ("Connector_Generic:Conn_02x10_Odd_Even", "Conn_02x10_Odd_Even", "nicklink:PinHeader_2x10_P2.54mm_Vertical_NoSilk", {
        "1": "+3.3V", "2": "GND",
        "3": "PA9", "4": "PA10", "5": "PA8", "6": "PA15",
        "7": "PA13", "8": "PA14", "9": "PB3", "10": "NRST",
        "11": "PB4", "12": "PB5", "13": "PB6", "14": "PB7",
        "15": "PB8", "16": "PB9", "17": "PC13", "18": "PC14",
        "19": "PC15", "20": "GND",
    }, {"MPN": "HanElectricity 2541WV-2x10P (male, 6 mm pins, 3 mm tail)"}),
}

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
# Friendly function names for docs/silkscreen
ALIASES = {
    "PA13": "SWDIO", "PA14": "SWCLK", "PB3": "SWO", "PA9": "UART1 TX", "PA10": "UART1 RX",
    "PB6": "I2C1 SCL (4.7k pull-up, IMU)", "PB7": "I2C1 SDA (4.7k pull-up, IMU)", "PB8": "CAN RX (remap)", "PB9": "CAN TX (remap)",
    "PA5": "SPI1 SCK", "PA6": "SPI1 MISO", "PA7": "SPI1 MOSI", "PB2": "BOOT1, 10k pull-down",
    "PC13": "user LED (active low)", "PA2": "UART2 TX", "PA3": "UART2 RX", "PA0": "WKUP / IMU INT1 via 10k",
    "PB10": "I2C2 SCL / UART3 TX", "PB11": "I2C2 SDA / UART3 RX",
    "PB13": "SPI2 SCK", "PB14": "SPI2 MISO", "PB15": "SPI2 MOSI",
}

POWER_NETS = {"GND", "+3.3V", "+3.3VA", "+5V", "VBUS"}
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
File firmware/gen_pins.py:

#!/usr/bin/env python3
"""Generate build/pins.h from tools/spec.py so the firmware's pin map can't drift from the hardware.

Also cross-checks spec.py against the STM32F103 LQFP-48 datasheet pinout: every
MCU pin whose net is named after a GPIO must sit on that GPIO's package pin.
"""
import os, re, sys

sys.path.insert(0, os.path.join(os.path.dirname(os.path.abspath(__file__)), "..", "tools"))
import spec  # noqa: E402

# DS5319 Table 5, LQFP48 column
LQFP48 = [None, "VBAT", "PC13", "PC14", "PC15", "PD0", "PD1", "NRST", "VSSA", "VDDA",
          "PA0", "PA1", "PA2", "PA3", "PA4", "PA5", "PA6", "PA7", "PB0", "PB1", "PB2",
          "PB10", "PB11", "VSS", "VDD", "PB12", "PB13", "PB14", "PB15", "PA8", "PA9", "PA10",
          "PA11", "PA12", "PA13", "VSS", "VDD", "PA14", "PA15", "PB3", "PB4", "PB5", "PB6",
          "PB7", "BOOT0", "PB8", "PB9", "VSS", "VDD"]
GPIO = re.compile(r"^P([A-D])(\d+)$")

parts = spec.PARTS
mcu = parts["U1"][3]
assert len(mcu) == 48, len(mcu)
for p, net in mcu.items():
    if GPIO.match(net):
        assert LQFP48[int(p)] == net, f"U1.{p} is {LQFP48[int(p)]} but spec net is {net}"

hdr = {}  # net -> "J1.19"
for ref in ("J1", "J3"):
    for p, net in parts[ref][3].items():
        hdr.setdefault(net, f"{ref}.{p}")


def loads(net):
    """On-board parts on this net other than the MCU and headers, e.g. 'R8 10k'."""
    out = []
    for ref, (_, val, _, pins, _) in sorted(parts.items()):
        if ref in ("U1", "J1", "J3"):
            continue
        nets = list(pins.values())
        if net in nets:
            other = sorted({n for n in nets if n != net})
            out.append(f"{ref} {val.split('_')[0]}" + (f" to {'/'.join(other)}" if len(other) == 1 else ""))
    return ", ".join(out)


def c(s):
    return '"' + s.replace('"', '\\"') + '"'


rows, walk = [], []
for p in range(1, 49):
    net = mcu[str(p)]
    fn = LQFP48[p]
    m = GPIO.match(fn)
    port, pin = ("ABCD".index(m.group(1)), int(m.group(2))) if m else (0xFF, 0)
    rows.append(f"  {{{p}, {c(fn)}, {c(net)}, {c(hdr.get(net, '') if net not in spec.POWER_NETS else '')}, {c(spec.ALIASES.get(net, ''))}, "
                f"{c(loads(net) if net not in spec.POWER_NETS else '')}, {port}, {pin}}},")

for ref in ("J1", "J3"):
    for p, net in sorted(parts[ref][3].items(), key=lambda kv: int(kv[0])):
        m = GPIO.match(net)
        if m:
            walk.append(f"  {{{c(net)}, {c(f'{ref}.{p}')}, {'ABCD'.index(m.group(1))}, {int(m.group(2))}}},")

print(f"""/* GENERATED by gen_pins.py from tools/spec.py (rev {spec.REV}) -- do not edit */
#pragma once
#include <stdint.h>
#define BOARD_REV "{spec.REV}"
typedef struct {{ uint8_t lqfp; const char *fn, *net, *hdr, *alias, *loads; uint8_t port, pin; }} mcu_pin_t;
typedef struct {{ const char *name, *hdr; uint8_t port, pin; }} hdr_pin_t;
static const mcu_pin_t MCU_PINS[] = {{
{chr(10).join(rows)}
}};
/* header GPIOs in header order (J1 then J3) */
static const hdr_pin_t HDR_PINS[] = {{
{chr(10).join(walk)}
}};
#define N_MCU_PINS (sizeof MCU_PINS / sizeof MCU_PINS[0])
#define N_HDR_PINS (sizeof HDR_PINS / sizeof HDR_PINS[0])""")
assert len(walk) == 33, len(walk)
